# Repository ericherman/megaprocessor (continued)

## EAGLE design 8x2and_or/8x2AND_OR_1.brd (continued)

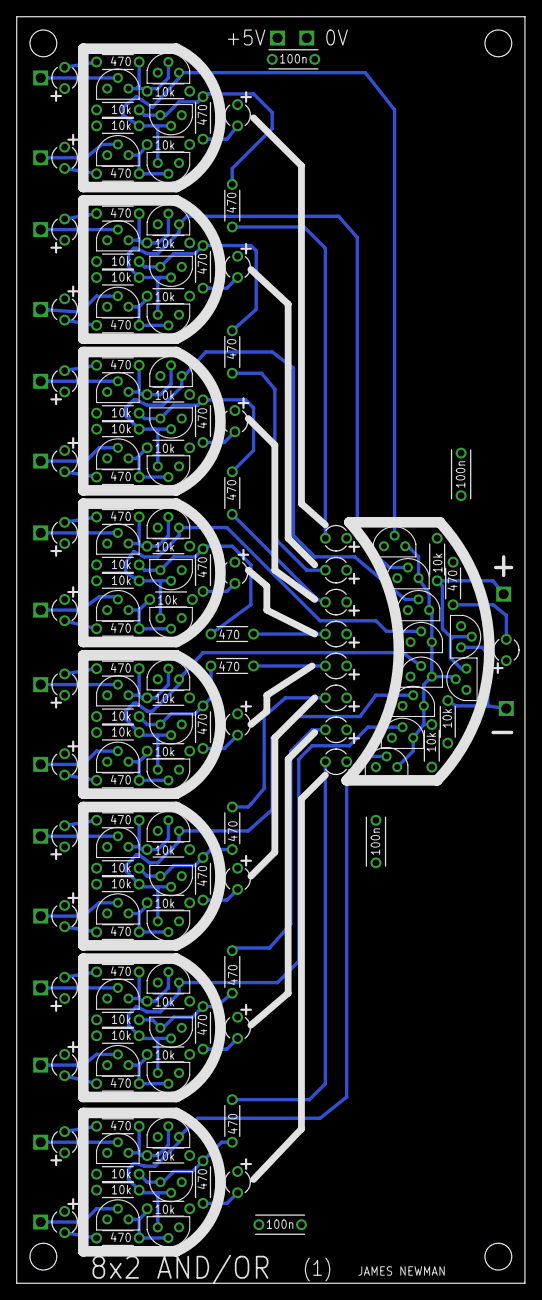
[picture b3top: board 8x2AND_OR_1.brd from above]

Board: 4 copper layers, 60.6 x 151.1 mm, 179 parts (0 on the bottom side), 86 nets.

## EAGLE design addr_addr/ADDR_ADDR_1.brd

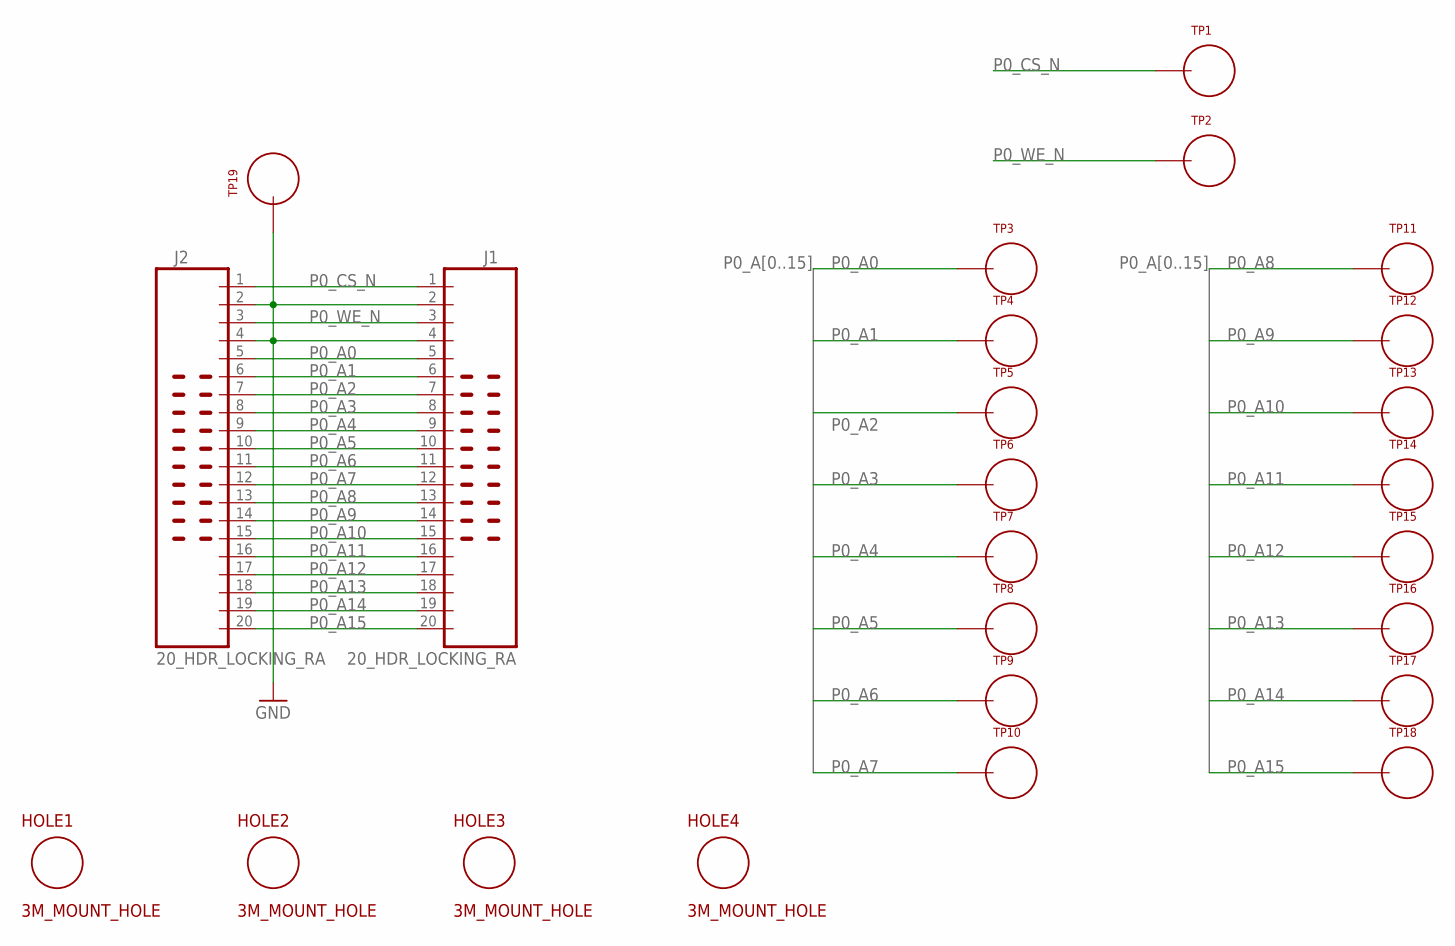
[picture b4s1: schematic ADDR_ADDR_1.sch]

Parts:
HOLE1, HOLE2, HOLE3, HOLE4: 3M_MOUNT_HOLE; 3M_HOLE
J1, J2: 20_HDR_LOCKING_RA
TP1, TP2, TP3, TP4, TP5, TP6, TP7, TP8, TP9, TP10, TP11, TP12, TP13, TP14, TP15, TP16, TP17, TP18, TP19: TEST_LOOP

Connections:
GND: J1.2, J1.4, J2.2, J2.4, TP19.P$1
P0_A0: J1.5, J2.5, TP3.P$1
P0_A1: J1.6, J2.6, TP4.P$1
P0_A2: J1.7, J2.7, TP5.P$1
P0_A3: J1.8, J2.8, TP6.P$1
P0_A4: J1.9, J2.9, TP7.P$1
P0_A5: J1.10, J2.10, TP8.P$1
P0_A6: J1.11, J2.11, TP9.P$1
P0_A7: J1.12, J2.12, TP10.P$1
P0_A8: J1.13, J2.13, TP11.P$1
P0_A9: J1.14, J2.14, TP12.P$1
P0_A10: J1.15, J2.15, TP13.P$1
P0_A11: J1.16, J2.16, TP14.P$1
P0_A12: J1.17, J2.17, TP15.P$1
P0_A13: J1.18, J2.18, TP16.P$1
P0_A14: J1.19, J2.19, TP17.P$1
P0_A15: J1.20, J2.20, TP18.P$1
P0_CS_N: J1.1, J2.1, TP1.P$1
P0_WE_N: J1.3, J2.3, TP2.P$1

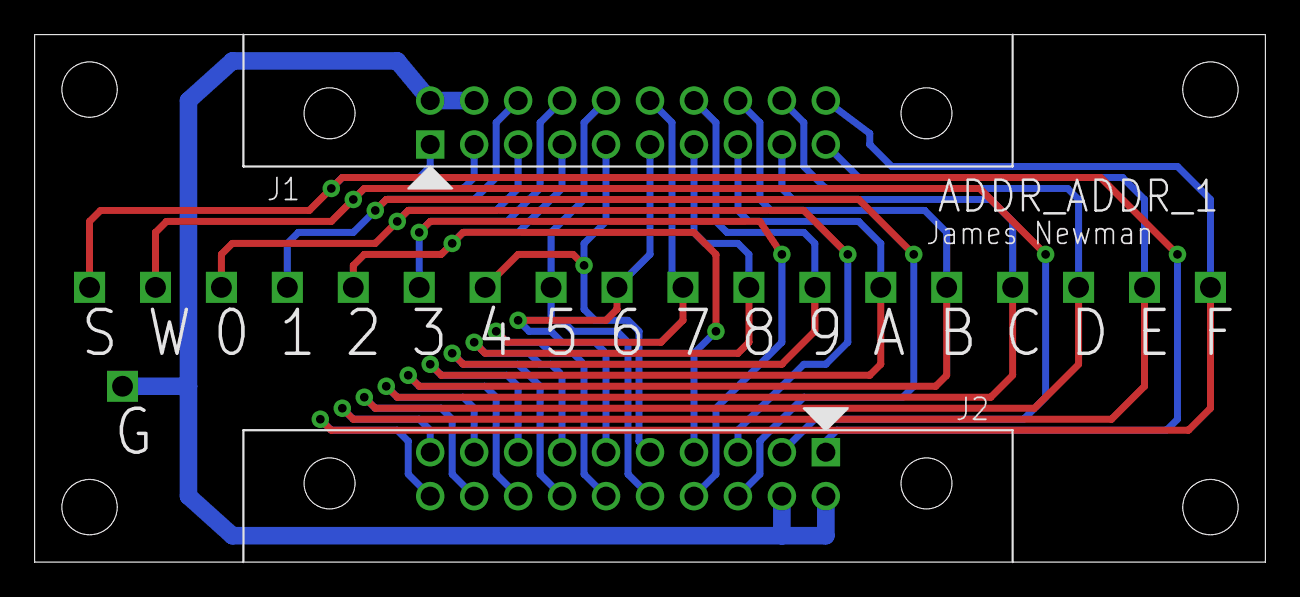
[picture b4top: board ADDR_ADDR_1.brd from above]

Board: 2 copper layers, 71.1 x 30.5 mm, 25 parts (0 on the bottom side), 19 nets.

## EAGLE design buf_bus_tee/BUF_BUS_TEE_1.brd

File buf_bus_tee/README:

Data bus Tee (buffered)

I use this when I want to tee a bus to send it to a different frame.

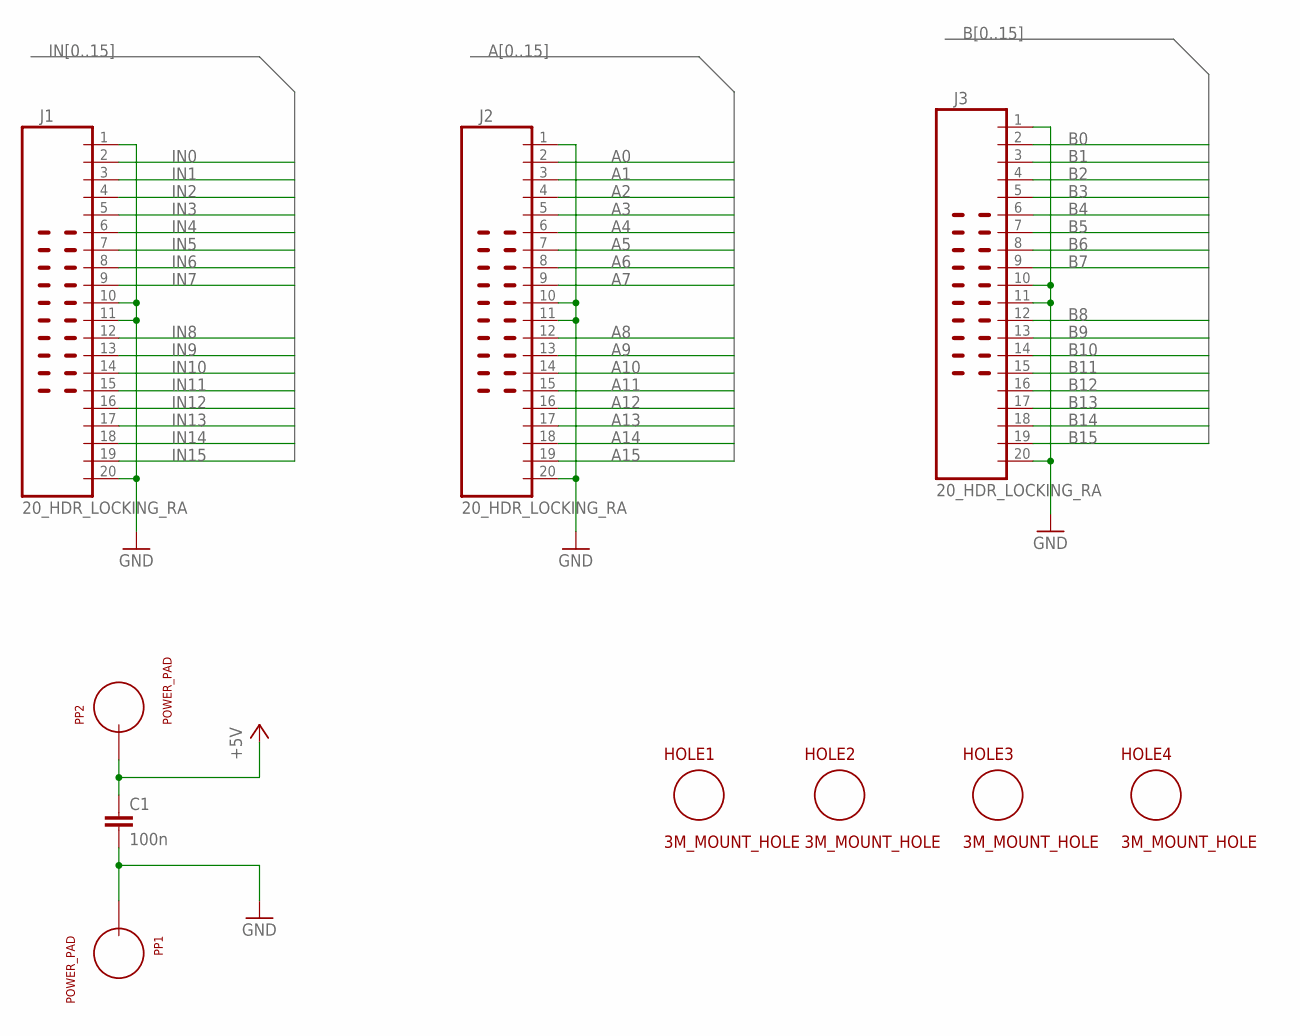
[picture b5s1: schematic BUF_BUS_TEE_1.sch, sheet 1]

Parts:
C1: 100n; CAP_P2INCH
HOLE1, HOLE2, HOLE3, HOLE4: 3M_MOUNT_HOLE; 3M_HOLE
J1, J2, J3: 20_HDR_LOCKING_RA
PP1, PP2: POWER_PAD

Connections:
+5V: C1.1, PP2.1; also elsewhere on the board
A0: J2.2; also elsewhere on the board
A1: J2.3; also elsewhere on the board
A2: J2.4; also elsewhere on the board
A3: J2.5; also elsewhere on the board
A4: J2.6; also elsewhere on the board
A5: J2.7; also elsewhere on the board
A6: J2.8; also elsewhere on the board
A7: J2.9; also elsewhere on the board
A8: J2.12; also elsewhere on the board
A9: J2.13; also elsewhere on the board
A10: J2.14; also elsewhere on the board
A11: J2.15; also elsewhere on the board
A12: J2.16; also elsewhere on the board
A13: J2.17; also elsewhere on the board
A14: J2.18; also elsewhere on the board
A15: J2.19; also elsewhere on the board
B0: J3.2; also elsewhere on the board
B1: J3.3; also elsewhere on the board
B2: J3.4; also elsewhere on the board
B3: J3.5; also elsewhere on the board
B4: J3.6; also elsewhere on the board
B5: J3.7; also elsewhere on the board
B6: J3.8; also elsewhere on the board
B7: J3.9; also elsewhere on the board
B8: J3.12; also elsewhere on the board
B9: J3.13; also elsewhere on the board
B10: J3.14; also elsewhere on the board
B11: J3.15; also elsewhere on the board
B12: J3.16; also elsewhere on the board
B13: J3.17; also elsewhere on the board
B14: J3.18; also elsewhere on the board
B15: J3.19; also elsewhere on the board
GND: C1.2, J1.1, J1.10, J1.11, J1.20, J2.1, J2.10, J2.11, J2.20, J3.1, J3.10, J3.11, J3.20, PP1.1; also elsewhere on the board
IN0: J1.2; also elsewhere on the board
IN1: J1.3; also elsewhere on the board
IN2: J1.4; also elsewhere on the board
IN3: J1.5; also elsewhere on the board
IN4: J1.6; also elsewhere on the board
IN5: J1.7; also elsewhere on the board
IN6: J1.8; also elsewhere on the board
IN7: J1.9; also elsewhere on the board
IN8: J1.12; also elsewhere on the board
IN9: J1.13; also elsewhere on the board
IN10: J1.14; also elsewhere on the board
IN11: J1.15; also elsewhere on the board
IN12: J1.16; also elsewhere on the board
IN13: J1.17; also elsewhere on the board
IN14: J1.18; also elsewhere on the board
IN15: J1.19; also elsewhere on the board

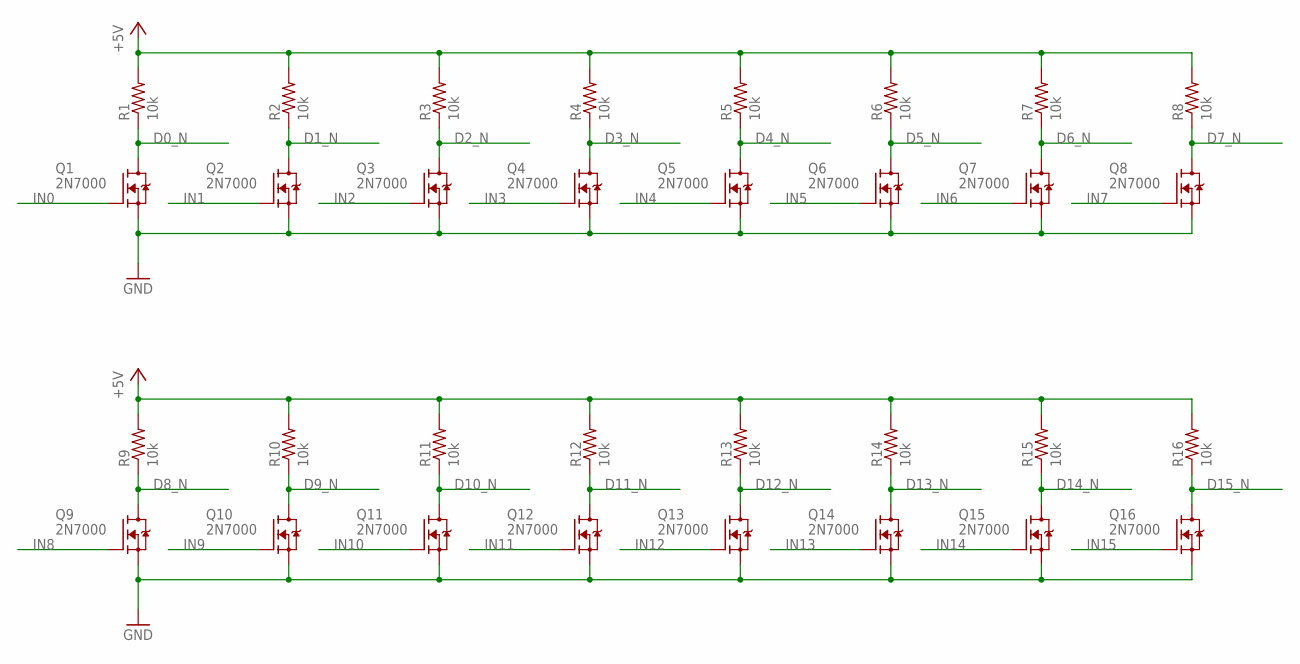
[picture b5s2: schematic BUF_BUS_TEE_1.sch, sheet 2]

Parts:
Q1, Q2, Q3, Q4, Q5, Q6, Q7, Q8, Q9, Q10, Q11, Q12, Q13, Q14, Q15, Q16: 2N7000; TO92-DGS
R1, R2, R3, R4, R5, R6, R7, R8, R9, R10, R11, R12, R13, R14, R15, R16: 10k; R_P2INCH

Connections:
+5V: R1.2, R2.2, R3.2, R4.2, R5.2, R6.2, R7.2, R8.2, R9.2, R10.2, R11.2, R12.2, R13.2, R14.2, R15.2, R16.2; also elsewhere on the board
D0_N: Q1.D, R1.1; also elsewhere on the board
D1_N: Q2.D, R2.1; also elsewhere on the board
D2_N: Q3.D, R3.1; also elsewhere on the board
D3_N: Q4.D, R4.1; also elsewhere on the board
D4_N: Q5.D, R5.1; also elsewhere on the board
D5_N: Q6.D, R6.1; also elsewhere on the board
D6_N: Q7.D, R7.1; also elsewhere on the board
D7_N: Q8.D, R8.1; also elsewhere on the board
D8_N: Q9.D, R9.1; also elsewhere on the board
D9_N: Q10.D, R10.1; also elsewhere on the board
D10_N: Q11.D, R11.1; also elsewhere on the board
D11_N: Q12.D, R12.1; also elsewhere on the board
D12_N: Q13.D, R13.1; also elsewhere on the board
D13_N: Q14.D, R14.1; also elsewhere on the board
D14_N: Q15.D, R15.1; also elsewhere on the board
D15_N: Q16.D, R16.1; also elsewhere on the board
GND: Q1.S, Q2.S, Q3.S, Q4.S, Q5.S, Q6.S, Q7.S, Q8.S, Q9.S, Q10.S, Q11.S, Q12.S, Q13.S, Q14.S, Q15.S, Q16.S; also elsewhere on the board
IN0: Q1.G; also elsewhere on the board
IN1: Q2.G; also elsewhere on the board
IN2: Q3.G; also elsewhere on the board
IN3: Q4.G; also elsewhere on the board
IN4: Q5.G; also elsewhere on the board
IN5: Q6.G; also elsewhere on the board
IN6: Q7.G; also elsewhere on the board
IN7: Q8.G; also elsewhere on the board
IN8: Q9.G; also elsewhere on the board
IN9: Q10.G; also elsewhere on the board
IN10: Q11.G; also elsewhere on the board
IN11: Q12.G; also elsewhere on the board
IN12: Q13.G; also elsewhere on the board
IN13: Q14.G; also elsewhere on the board
IN14: Q15.G; also elsewhere on the board
IN15: Q16.G; also elsewhere on the board

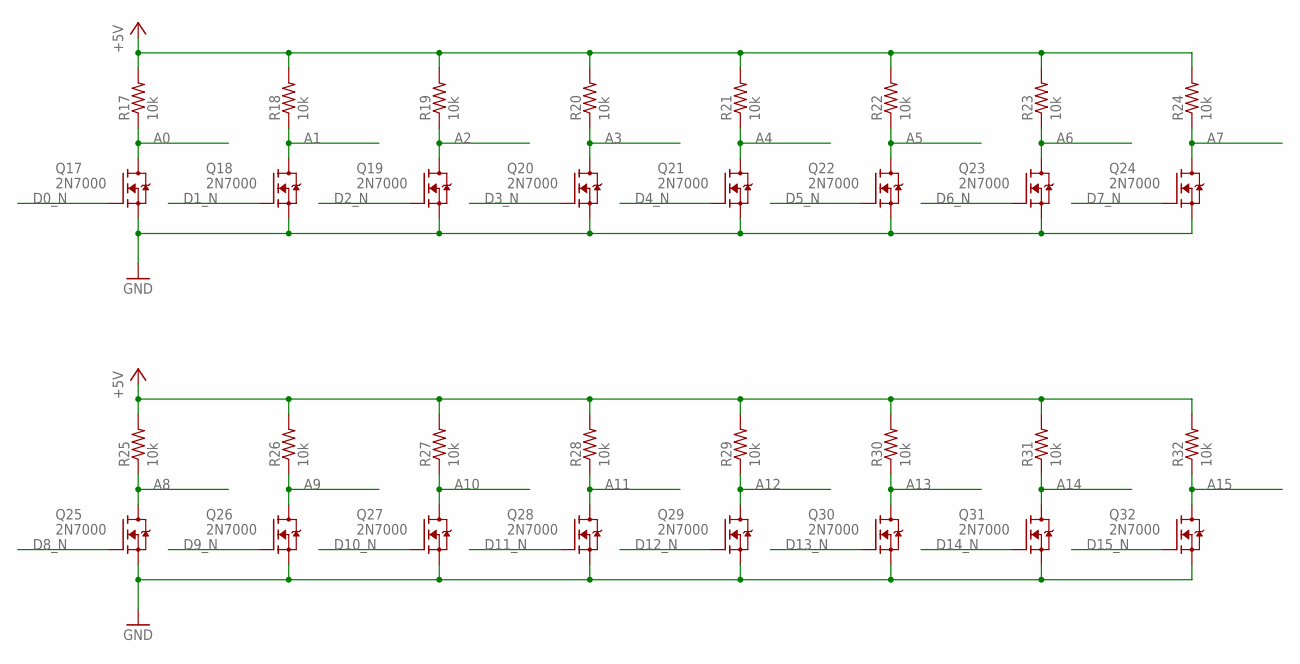
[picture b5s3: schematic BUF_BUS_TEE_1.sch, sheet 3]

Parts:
Q17, Q18, Q19, Q20, Q21, Q22, Q23, Q24, Q25, Q26, Q27, Q28, Q29, Q30, Q31, Q32: 2N7000; TO92-DGS
R17, R18, R19, R20, R21, R22, R23, R24, R25, R26, R27, R28, R29, R30, R31, R32: 10k; R_P2INCH

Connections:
+5V: R17.2, R18.2, R19.2, R20.2, R21.2, R22.2, R23.2, R24.2, R25.2, R26.2, R27.2, R28.2, R29.2, R30.2, R31.2, R32.2; also elsewhere on the board
A0: Q17.D, R17.1; also elsewhere on the board
A1: Q18.D, R18.1; also elsewhere on the board
A2: Q19.D, R19.1; also elsewhere on the board
A3: Q20.D, R20.1; also elsewhere on the board
A4: Q21.D, R21.1; also elsewhere on the board
A5: Q22.D, R22.1; also elsewhere on the board
A6: Q23.D, R23.1; also elsewhere on the board
A7: Q24.D, R24.1; also elsewhere on the board
A8: Q25.D, R25.1; also elsewhere on the board
A9: Q26.D, R26.1; also elsewhere on the board
A10: Q27.D, R27.1; also elsewhere on the board
A11: Q28.D, R28.1; also elsewhere on the board
A12: Q29.D, R29.1; also elsewhere on the board
A13: Q30.D, R30.1; also elsewhere on the board
A14: Q31.D, R31.1; also elsewhere on the board
A15: Q32.D, R32.1; also elsewhere on the board
D0_N: Q17.G; also elsewhere on the board
D1_N: Q18.G; also elsewhere on the board
D2_N: Q19.G; also elsewhere on the board
D3_N: Q20.G; also elsewhere on the board
D4_N: Q21.G; also elsewhere on the board
D5_N: Q22.G; also elsewhere on the board
D6_N: Q23.G; also elsewhere on the board
D7_N: Q24.G; also elsewhere on the board
D8_N: Q25.G; also elsewhere on the board
D9_N: Q26.G; also elsewhere on the board
D10_N: Q27.G; also elsewhere on the board
D11_N: Q28.G; also elsewhere on the board
D12_N: Q29.G; also elsewhere on the board
D13_N: Q30.G; also elsewhere on the board
D14_N: Q31.G; also elsewhere on the board
D15_N: Q32.G; also elsewhere on the board
GND: Q17.S, Q18.S, Q19.S, Q20.S, Q21.S, Q22.S, Q23.S, Q24.S, Q25.S, Q26.S, Q27.S, Q28.S, Q29.S, Q30.S, Q31.S, Q32.S; also elsewhere on the board

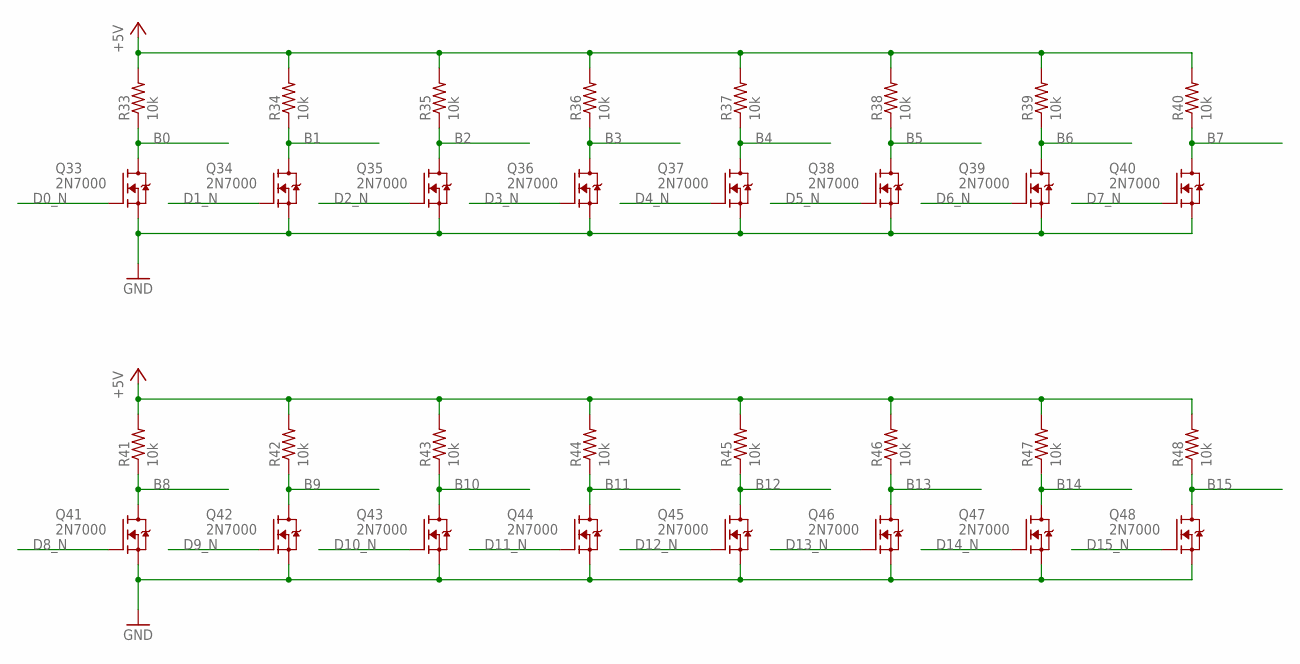
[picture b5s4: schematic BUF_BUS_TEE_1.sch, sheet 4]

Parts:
Q33, Q34, Q35, Q36, Q37, Q38, Q39, Q40, Q41, Q42, Q43, Q44, Q45, Q46, Q47, Q48: 2N7000; TO92-DGS
R33, R34, R35, R36, R37, R38, R39, R40, R41, R42, R43, R44, R45, R46, R47, R48: 10k; R_P2INCH

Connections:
+5V: R33.2, R34.2, R35.2, R36.2, R37.2, R38.2, R39.2, R40.2, R41.2, R42.2, R43.2, R44.2, R45.2, R46.2, R47.2, R48.2; also elsewhere on the board
B0: Q33.D, R33.1; also elsewhere on the board
B1: Q34.D, R34.1; also elsewhere on the board
B2: Q35.D, R35.1; also elsewhere on the board
B3: Q36.D, R36.1; also elsewhere on the board
B4: Q37.D, R37.1; also elsewhere on the board
B5: Q38.D, R38.1; also elsewhere on the board
B6: Q39.D, R39.1; also elsewhere on the board
B7: Q40.D, R40.1; also elsewhere on the board
B8: Q41.D, R41.1; also elsewhere on the board
B9: Q42.D, R42.1; also elsewhere on the board
B10: Q43.D, R43.1; also elsewhere on the board
B11: Q44.D, R44.1; also elsewhere on the board
B12: Q45.D, R45.1; also elsewhere on the board
B13: Q46.D, R46.1; also elsewhere on the board
B14: Q47.D, R47.1; also elsewhere on the board
B15: Q48.D, R48.1; also elsewhere on the board
D0_N: Q33.G; also elsewhere on the board
D1_N: Q34.G; also elsewhere on the board
D2_N: Q35.G; also elsewhere on the board
D3_N: Q36.G; also elsewhere on the board
D4_N: Q37.G; also elsewhere on the board
D5_N: Q38.G; also elsewhere on the board
D6_N: Q39.G; also elsewhere on the board
D7_N: Q40.G; also elsewhere on the board
D8_N: Q41.G; also elsewhere on the board
D9_N: Q42.G; also elsewhere on the board
D10_N: Q43.G; also elsewhere on the board
D11_N: Q44.G; also elsewhere on the board
D12_N: Q45.G; also elsewhere on the board
D13_N: Q46.G; also elsewhere on the board
D14_N: Q47.G; also elsewhere on the board
D15_N: Q48.G; also elsewhere on the board
GND: Q33.S, Q34.S, Q35.S, Q36.S, Q37.S, Q38.S, Q39.S, Q40.S, Q41.S, Q42.S, Q43.S, Q44.S, Q45.S, Q46.S, Q47.S, Q48.S; also elsewhere on the board

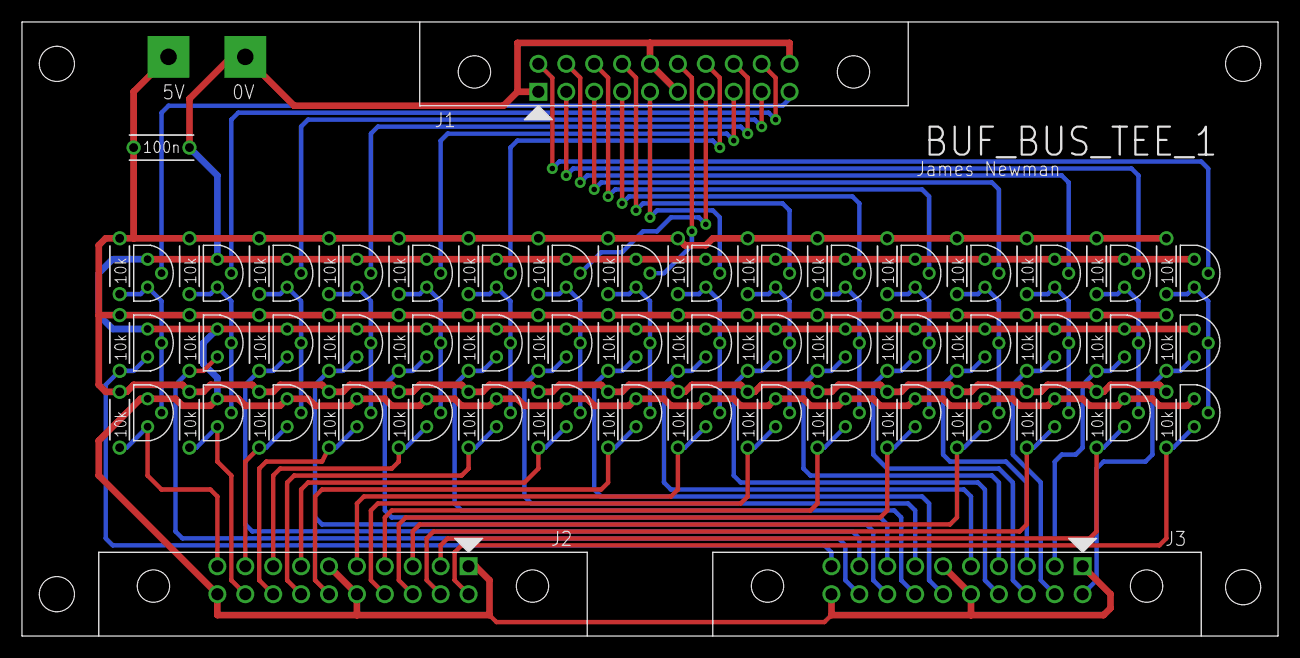
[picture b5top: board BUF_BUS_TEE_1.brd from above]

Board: 2 copper layers, 114.3 x 55.9 mm, 106 parts (0 on the bottom side), 66 nets.

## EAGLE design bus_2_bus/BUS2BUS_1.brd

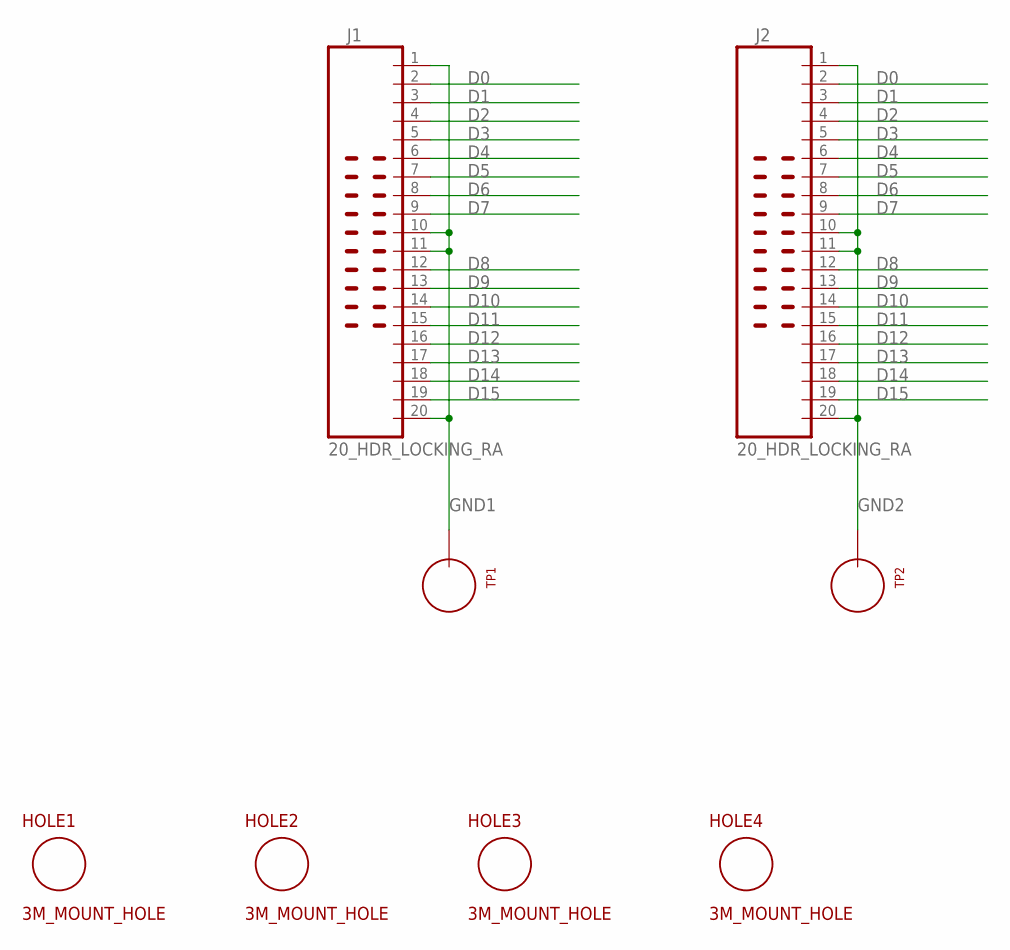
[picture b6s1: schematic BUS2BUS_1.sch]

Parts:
HOLE1, HOLE2, HOLE3, HOLE4: 3M_MOUNT_HOLE; 3M_HOLE
J1, J2: 20_HDR_LOCKING_RA
TP1, TP2: TEST_LOOP

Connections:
D0: J1.2, J2.2
D1: J1.3, J2.3
D2: J1.4, J2.4
D3: J1.5, J2.5
D4: J1.6, J2.6
D5: J1.7, J2.7
D6: J1.8, J2.8
D7: J1.9, J2.9
D8: J1.12, J2.12
D9: J1.13, J2.13
D10: J1.14, J2.14
D11: J1.15, J2.15
D12: J1.16, J2.16
D13: J1.17, J2.17
D14: J1.18, J2.18
D15: J1.19, J2.19
GND1: J1.1, J1.10, J1.11, J1.20, TP1.P$1
GND2: J2.1, J2.10, J2.11, J2.20, TP2.P$1

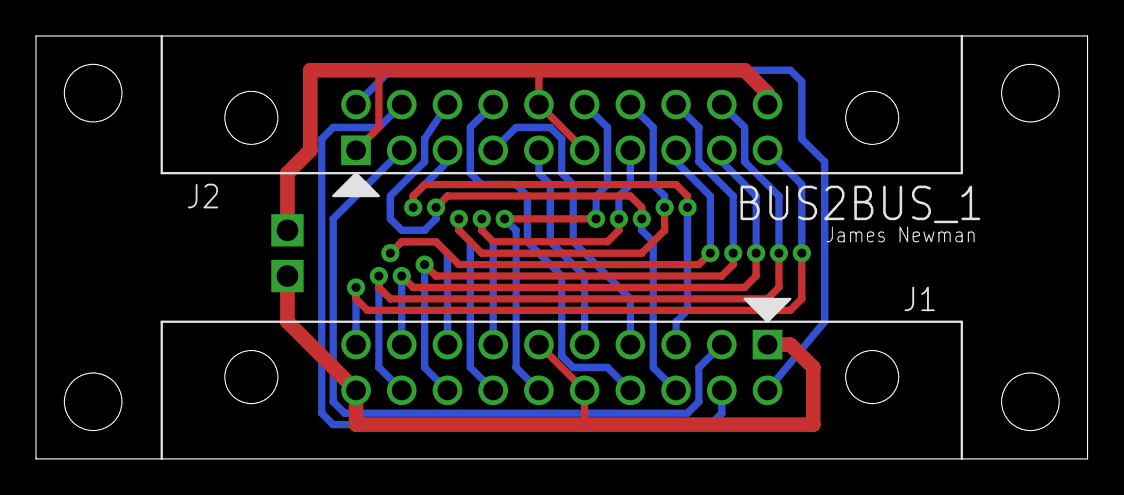
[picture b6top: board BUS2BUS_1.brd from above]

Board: 2 copper layers, 58.4 x 23.5 mm, 8 parts (0 on the bottom side), 18 nets.

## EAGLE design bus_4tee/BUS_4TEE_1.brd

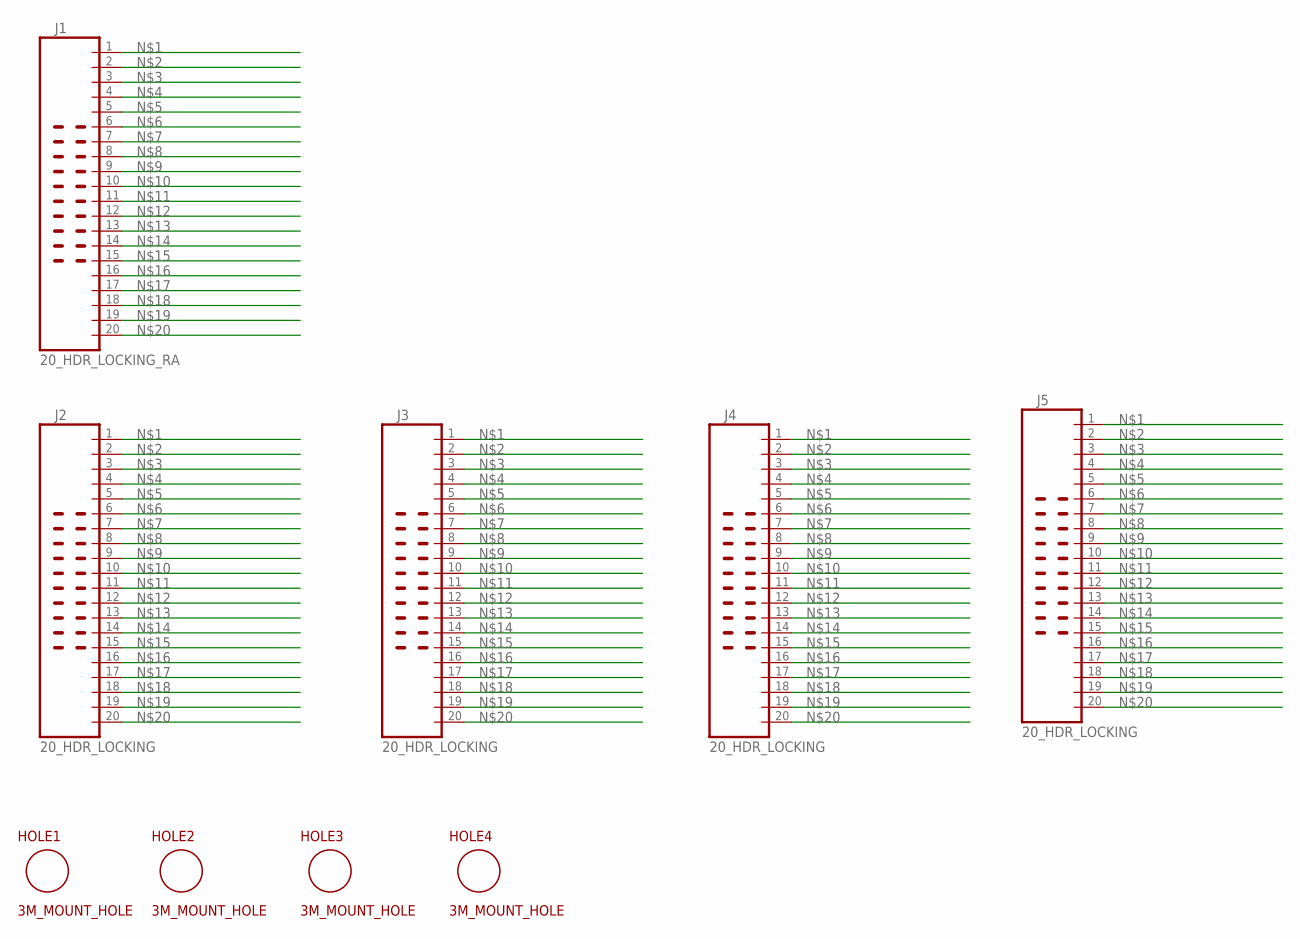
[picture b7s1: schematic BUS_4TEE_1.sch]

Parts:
HOLE1, HOLE2, HOLE3, HOLE4: 3M_MOUNT_HOLE; 3M_HOLE
J1: 20_HDR_LOCKING_RA
J2, J3, J4, J5: 20_HDR_LOCKING

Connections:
unnamed: J1.1, J2.1, J3.1, J4.1, J5.1
unnamed: J1.2, J2.2, J3.2, J4.2, J5.2
unnamed: J1.3, J2.3, J3.3, J4.3, J5.3
unnamed: J1.4, J2.4, J3.4, J4.4, J5.4
unnamed: J1.5, J2.5, J3.5, J4.5, J5.5
unnamed: J1.6, J2.6, J3.6, J4.6, J5.6
unnamed: J1.7, J2.7, J3.7, J4.7, J5.7
unnamed: J1.8, J2.8, J3.8, J4.8, J5.8
unnamed: J1.9, J2.9, J3.9, J4.9, J5.9
unnamed: J1.10, J2.10, J3.10, J4.10, J5.10
unnamed: J1.11, J2.11, J3.11, J4.11, J5.11
unnamed: J1.12, J2.12, J3.12, J4.12, J5.12
unnamed: J1.13, J2.13, J3.13, J4.13, J5.13
unnamed: J1.14, J2.14, J3.14, J4.14, J5.14
unnamed: J1.15, J2.15, J3.15, J4.15, J5.15
unnamed: J1.16, J2.16, J3.16, J4.16, J5.16
unnamed: J1.17, J2.17, J3.17, J4.17, J5.17
unnamed: J1.18, J2.18, J3.18, J4.18, J5.18
unnamed: J1.19, J2.19, J3.19, J4.19, J5.19
unnamed: J1.20, J2.20, J3.20, J4.20, J5.20

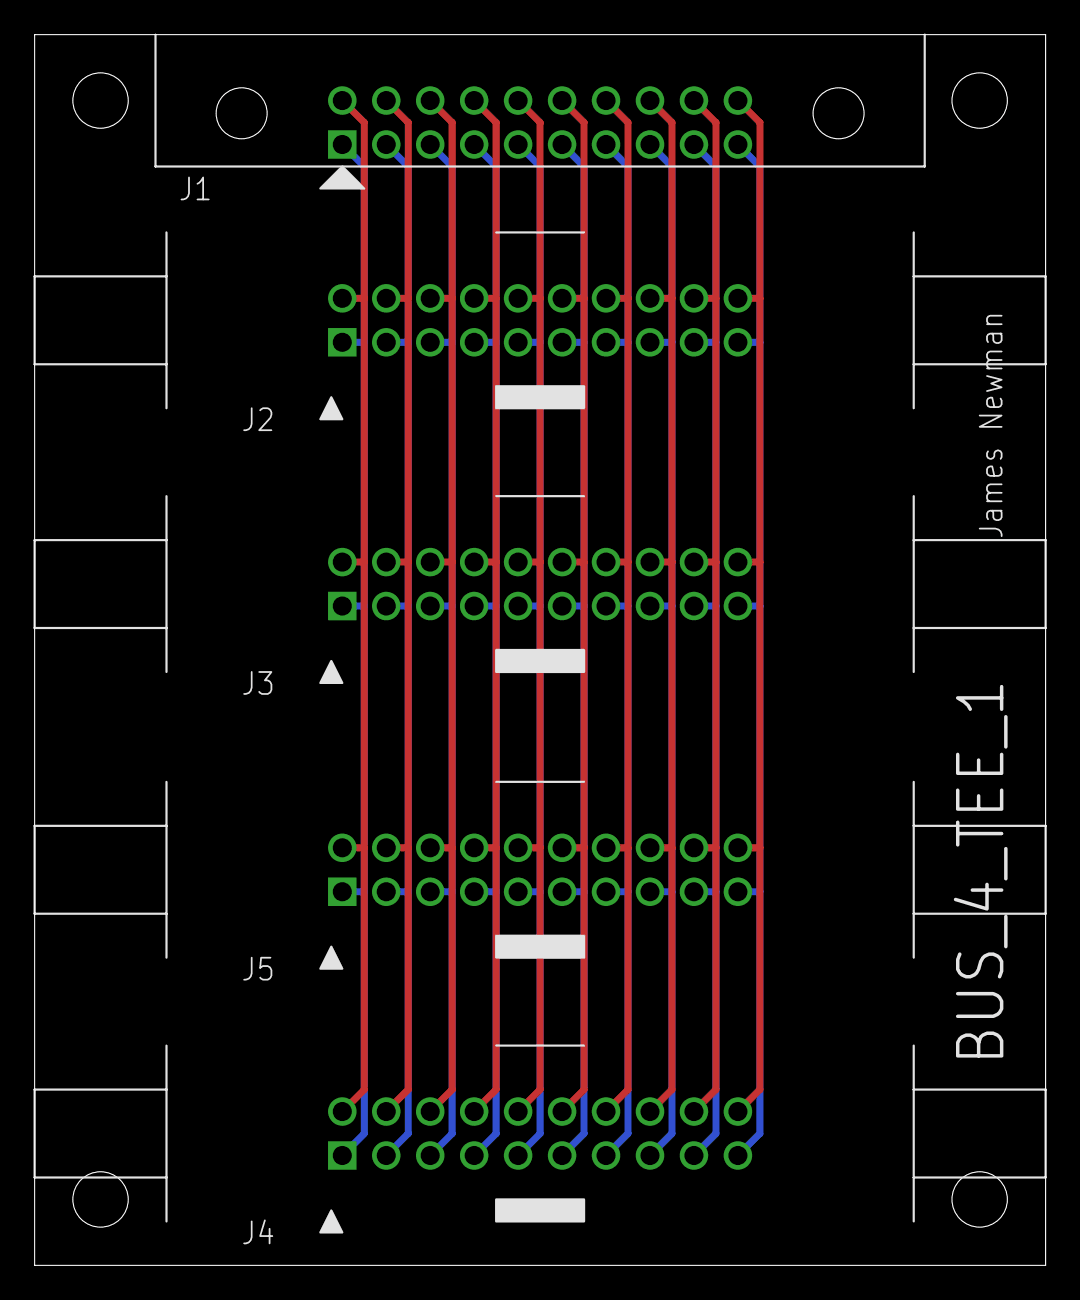
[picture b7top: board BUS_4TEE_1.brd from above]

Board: 2 copper layers, 58.4 x 71.1 mm, 9 parts (0 on the bottom side), 20 nets.
